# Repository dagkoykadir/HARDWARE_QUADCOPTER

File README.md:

# HARDWARE_QUADCOPTER
# HARDWARE_QUADCOPTER

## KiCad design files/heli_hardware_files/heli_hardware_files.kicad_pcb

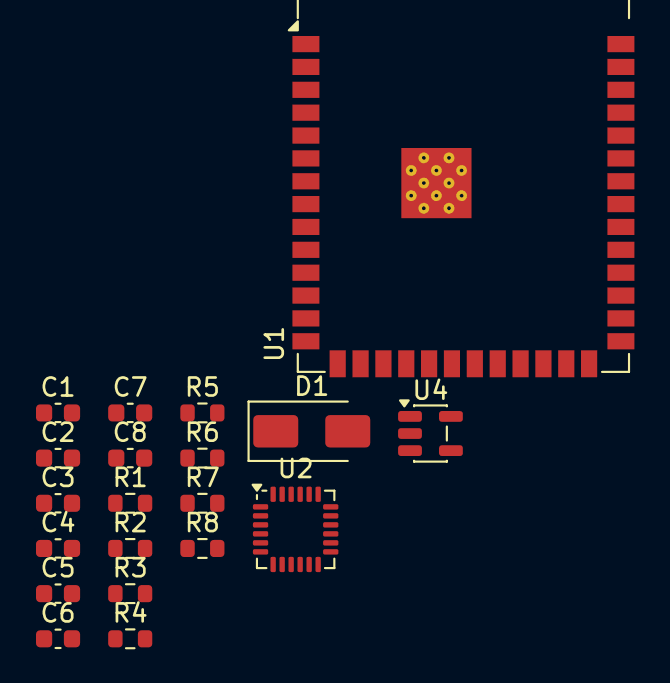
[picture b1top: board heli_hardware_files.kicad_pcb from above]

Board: 2 copper layers, 20 parts (0 on the bottom side), 11 nets, no tracks yet.

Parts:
C1, C2, C3: 0.1uF; C_0603_1608Metric
C4: 220pF; C_0603_1608Metric
C5, C8: 10uF; C_0603_1608Metric
C6: 470pF; C_0603_1608Metric
C7: 2.2uF; C_0603_1608Metric
D1: SS34; D_SMA
R1, R2, R3, R4, R7: 4.7k; R_0603_1608Metric
R5, R6: 5.1k; R_0603_1608Metric
R8: 470; R_0603_1608Metric
U1: ESP32-S3-WROOM-1-N8; ESP32-S3-WROOM-1
U2: MPU-6050; InvenSense_QFN-24_4x4mm_P0.5mm
U4: SPX3819M5-L-3-3; SOT-23-5

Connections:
+3.3V: C1.2, C2.1, C7.1, C8.1, R1.1, R2.1, R3.2, R4.2, R8.1, U2.8 (VLOGIC), U2.13 (VDD), U4.5 (OUT)
/SCL: R2.2, U2.23 (SCL)
/SDA: R1.2, U2.24 (SDA)
/XCL: R4.1, U2.7 (AUX_CL)
/XDA: R3.1, U2.6 (AUX_DA)
GND: C1.1, C2.2, C3.1, C4.2, C5.1, C6.1, C7.2, C8.2, R5.2, R6.2, R7.2, U1.1 (GND), U1.40 (GND), U2.1 (CLKIN), U2.11 (FSYNC), U2.18 (GND), U4.2 (GND)
unnamed: D1.2 (A), R7.1
unnamed: C5.2, D1.1 (K), U4.1 (IN)
unnamed: C4.1, U2.20 (CPOUT)
unnamed: C3.2, U2.10 (REGOUT)
unnamed: C6.2, U4.4 (BP)

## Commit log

2026-01-10 USB-C was added.
2026-01-11 Pcb was added.
2026-02-02 1/2/2026
